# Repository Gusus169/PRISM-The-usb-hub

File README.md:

# 'PRISM' The USB Hub V2.0

### A compact 4-port USB 2.0 hub PCB featuring ESD protection,  PTC resettable fuses, and per-port LED indicators; All packed in a small keychain design form.

[Key Features](#key-features) • [PCB](#pcb) • [BOM](#bom) • [License](#license)

## About

PRISM is a USB Type-C-based input USB hub that splits it into four downstream ports — just like a prism splits light. Built from scratch starting in EasyEDA Pro(V1), later moving to KiCad and finishing off with Blender animated renders, this project pushed me deep into reading datasheets, understanding circuit protection, and the difference between making something work and engineering something worth making.

## Key Features

- Main IC - SL2.1S (IC)
- Static Circuit Protection - ESD diodes on all ports
- Short-Circuit protection - PTC on all downstream ports
- Downstream port features - 2x USB-Type-C
                           - 2x USB-Type-A
- Upstream port - USB-Type-C
- Multi-Layer capacitor decoupling
- Compact 2-layer PCB, designed to be a keychain at ~3" × 1.2".

## PCB

Designed in EasyEDA Pro(V1), Further Refined in KiCad(V2).

### Schematic

### PCB

**Front:**

**Back:**

### KiCad Renders 

**Front:**

**Back:**

## BOM

|Index|	LCSC#	| Product Name|	Manufacturer|Package|	Design Refrence#|	Quantity|	Product Link|
|-----|-------|-------------|--------------|------|-----------------|---------|-------------|
|1	|C207022|	0805L050WR|	Littelfuse|	805|	F1,F2,F3,F4|	4|	https://www.lcsc.com/product-detail/C207022.html|
|2	|C668591|	10.0 QHHTZB6.3|	SHOU HAN|	SMD|	USB1,USB2	|2	|https://www.lcsc.com/product-detail/C668591.html|
|3	|C1591|	CL10B104KB8NNNC|	Samsung Electro-Mechanics|	603	|C1-8,C11-17|	15|https://www.lcsc.com/product-detail/C1591.html|
|4	|C2906982|	FRC0603F1002TS|	FOJAN|	603|	R1,R10,R2,R3,R4,R5,R6,R7,R8,R9|	10	|https://www.lcsc.com/product-detail/C2906982.html|
|5	|C2907035|	FRC0603F4R70TS|	FOJAN|	603|	R11|	1	|https://www.lcsc.com/product-detail/C2907035.html|
|6	|C2684433|	SL2.1s	|CoreChips|	SSOP-16|	U1|	1	|https://www.lcsc.com/product-detail/C2684433.html|
|7	|C2765186|TYPE-C 16PIN 2MD(073)|	SHOU HAN|	SMD	|USB0,USB3,USB4	|1	|https://www.lcsc.com/product-detail/C2765186.html|
|8	|C7519|	USBLC6-2SC6|	ST|	SOT-23-6L|	D0,D1,D2,D3,D4 |3	|https://www.lcsc.com/product-detail/C7519.html|
|9	|C965799|	XL-1608SURC-06|	XINGLIGHT	|603	|LED1,LED2,LED3,LED4|	5	|https://www.lcsc.com/product-detail/C965799.html|
|10|	C22367835|	HGC1206R5476M250NSPJ|	Chinocera|	1206|	C9|	4	|https://www.lcsc.com/product-detail/C22367835.html|

## What I Learned

- How to read the reference schematic provided by the manufacturer
- In-depth functionality of capacitors - Why they are used in pairs
- Functionality of ESD & PTC
- Difference in USB types and their speeds
- Differential pair routing and its importance

## Credits

This project uses:

- [EasyEDA Pro](https://pro.easyeda.com/) 
- [KiCad](https://www.kicad.org/download/)
- [JLCPCB](https://jlcpcb.com/) for PCB fabrication
- [LCSC](https://www.lcsc.com/) for component sourcing
- Based on the [Hack Club USB Hub guide](https://macondo.hackclub.com/docs/usb-hub)

## License

MIT

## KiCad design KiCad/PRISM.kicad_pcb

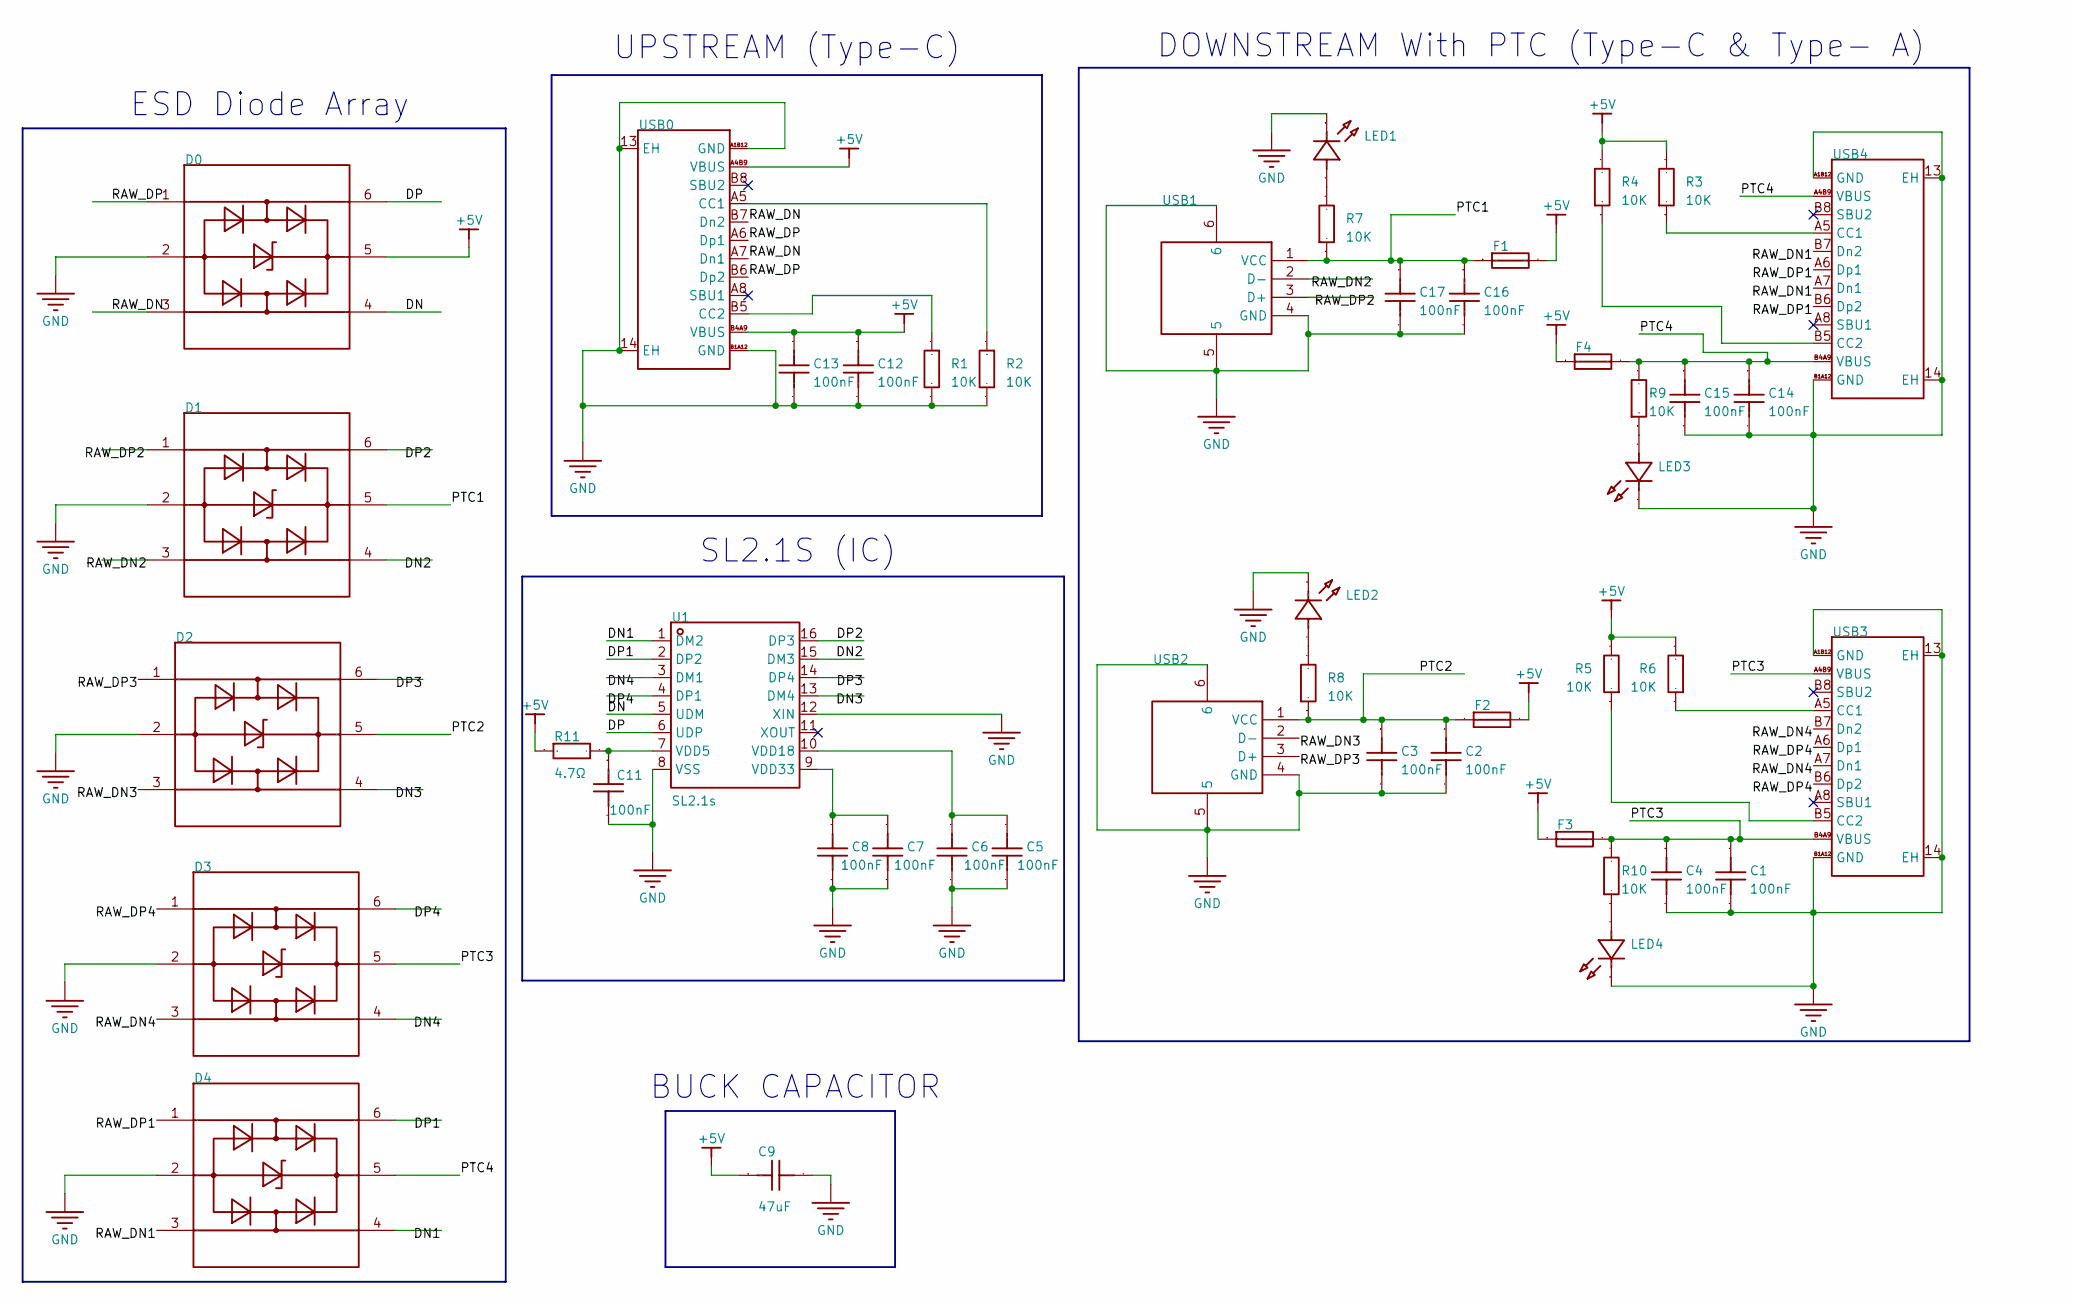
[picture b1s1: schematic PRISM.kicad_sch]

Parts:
C1, C2, C3, C4, C5, C6, C7, C8, C11, C12, C13, C14, C15, C16, C17: 100nF; C0603
C9: 47uF; C1206; Manufacturer Part TCC1206X5R476M100HT; LCSC Part Name 47uF ±20% 10V
D0, D1, D2, D3, D4: USBLC6-2SC6; SOT-23-6_L2.9-W1.6-P0.95-LS2.8-BL; Manufacturer Part USBLC6-2SC6; LCSC Part Name 单向ESD
F1, F2, F3, F4: 0805L050WR; R0805; Manufacturer Part 0805L050WR; LCSC Part Name 6V 500mA 0805自恢复
LED1, LED2, LED3, LED4: XL-1608SURC-06; LED0603-RD_RED; Manufacturer Part XL-1608SURC-06; LCSC Part Name 0603红色贴片式发光二极管
R1, R2, R3, R4, R5, R6, R7, R8, R9, R10: 10K; R0603
R11: 4.7Ω; R0603; Manufacturer Part 0603WAJ047JT5E; LCSC Part Name 4.7Ω ±5% 100mW 厚膜电阻
U1: SL2.1s; SSOP-16_L4.6-W2.6-P0.53-LS4.0-BL; Manufacturer Part SL2.1s; LCSC Part Name USB2.0 HUB控制器集成电路
USB0, USB3, USB4: TYPE-C 16PIN 2MD(073); USB-C-SMD_TYPE-C-16PIN-2MD-073; Manufacturer Part TYPE-C 16PIN 2MD(073); LCSC Part Name Type-C 母 卧贴
USB1, USB2: 10.0 QHHTZB6.3; USB-A-TH_10.0QHHTZB6.3; Manufacturer Part 10.0 QHHTZB6.3; LCSC Part Name 壳长10.0mm

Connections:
+5V: C9.1, C12.1, C13.1, D0.5, F1.2, F2.2, F3.1, F4.1, R3.2, R4.2, R5.2, R6.2, R11.1, USB0.A4B9 (VBUS), USB0.B4A9 (VBUS)
/DN: D0.4, U1.5 (UDM)
/DN1: D4.4, U1.1 (DM2)
/DN2: D1.4, U1.15 (DM3)
/DN3: D2.4, U1.13 (DM4)
/DN4: D3.4, U1.3 (DM1)
/DP: D0.6, U1.6 (UDP)
/DP1: D4.6, U1.2 (DP2)
/DP2: D1.6, U1.16 (DP3)
/DP3: D2.6, U1.14 (DP4)
/DP4: D3.6, U1.4 (DP1)
/PTC1: C16.1, C17.1, D1.5, F1.1, R7.1, USB1.1 (VCC)
/PTC2: C2.1, C3.1, D2.5, F2.1, R8.1, USB2.1 (VCC)
/PTC3: C1.1, C4.1, D3.5, F3.2, R10.2, USB3.A4B9 (VBUS), USB3.B4A9 (VBUS)
/PTC4: C14.1, C15.1, D4.5, F4.2, R9.2, USB4.A4B9 (VBUS), USB4.B4A9 (VBUS)
/RAW_DN: D0.3, USB0.A7 (Dn1), USB0.B7 (Dn2)
/RAW_DN1: D4.3, USB4.A7 (Dn1), USB4.B7 (Dn2)
/RAW_DN2: D1.3, USB1.2 (D-)
/RAW_DN3: D2.3, USB2.2 (D-)
/RAW_DN4: D3.3, USB3.A7 (Dn1), USB3.B7 (Dn2)
/RAW_DP: D0.1, USB0.A6 (Dp1), USB0.B6 (Dp2)
/RAW_DP1: D4.1, USB4.A6 (Dp1), USB4.B6 (Dp2)
/RAW_DP2: D1.1, USB1.3 (D+)
/RAW_DP3: D2.1, USB2.3 (D+)
/RAW_DP4: D3.1, USB3.A6 (Dp1), USB3.B6 (Dp2)
GND: C1.2, C2.2, C3.2, C4.2, C5.2, C6.2, C7.2, C8.2, C9.2, C11.2, C12.2, C13.2, C14.2, C15.2, C16.2, C17.2, D0.2, D1.2, D2.2, D3.2, D4.2, LED1.1 (K), LED2.1 (K), LED3.1 (K), LED4.1 (K), R1.2, R2.2, U1.8 (VSS), U1.12 (XIN), USB0.13 (EH), USB0.14 (EH), USB0.A1B12 (GND), USB0.B1A12 (GND), USB1.4 (GND), USB1.5, USB1.6, USB2.4 (GND), USB2.5, USB2.6, USB3.13 (EH), USB3.14 (EH), USB3.A1B12 (GND), USB3.B1A12 (GND), USB4.13 (EH), USB4.14 (EH), USB4.A1B12 (GND), USB4.B1A12 (GND)
unnamed: LED1.2 (A), R7.2
unnamed: LED2.2 (A), R8.2
unnamed: LED3.2 (A), R9.1
unnamed: LED4.2 (A), R10.1
unnamed: C11.1, R11.2, U1.7 (VDD5)
unnamed: C5.1, C6.1, U1.10 (VDD18)
unnamed: C7.1, C8.1, U1.9 (VDD33)
unnamed: R2.1, USB0.A5 (CC1)
unnamed: R1.1, USB0.B5 (CC2)
unnamed: R6.1, USB3.A5 (CC1)
unnamed: R5.1, USB3.B5 (CC2)
unnamed: R3.1, USB4.A5 (CC1)
unnamed: R4.1, USB4.B5 (CC2)

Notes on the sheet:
ESD Diode Array
DOWNSTREAM With PTC (Type-C & Type- A)
BUCK CAPACITOR
UPSTREAM (Type-C)
SL2.1S (IC)

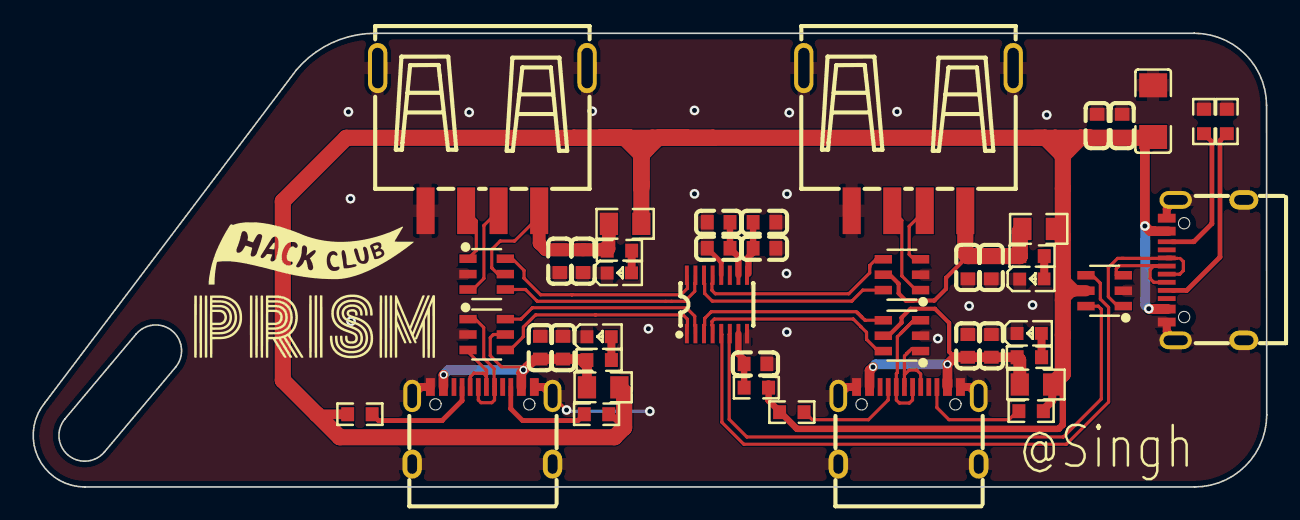
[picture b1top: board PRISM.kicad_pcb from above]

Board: 2 copper layers, 76.0 x 28.0 mm, 46 parts (0 on the bottom side), 39 nets.

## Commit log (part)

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2026-06-29 README
    Updated project title and expanded description with key features, PCB design details, BOM, and lessons learned.
2026-06-30 FILES
